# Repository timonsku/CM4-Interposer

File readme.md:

CM4 Interposer
===
Untested design as of 12th September 2021
---

A PCB that helps save the connector cycles on a CM4 by passing through its connection to a second set of Hirose connectors.

Needs:
- 2x DF40C-100DS-0.4V(51)
- 2x DF40C-100DP-0.4V(51)

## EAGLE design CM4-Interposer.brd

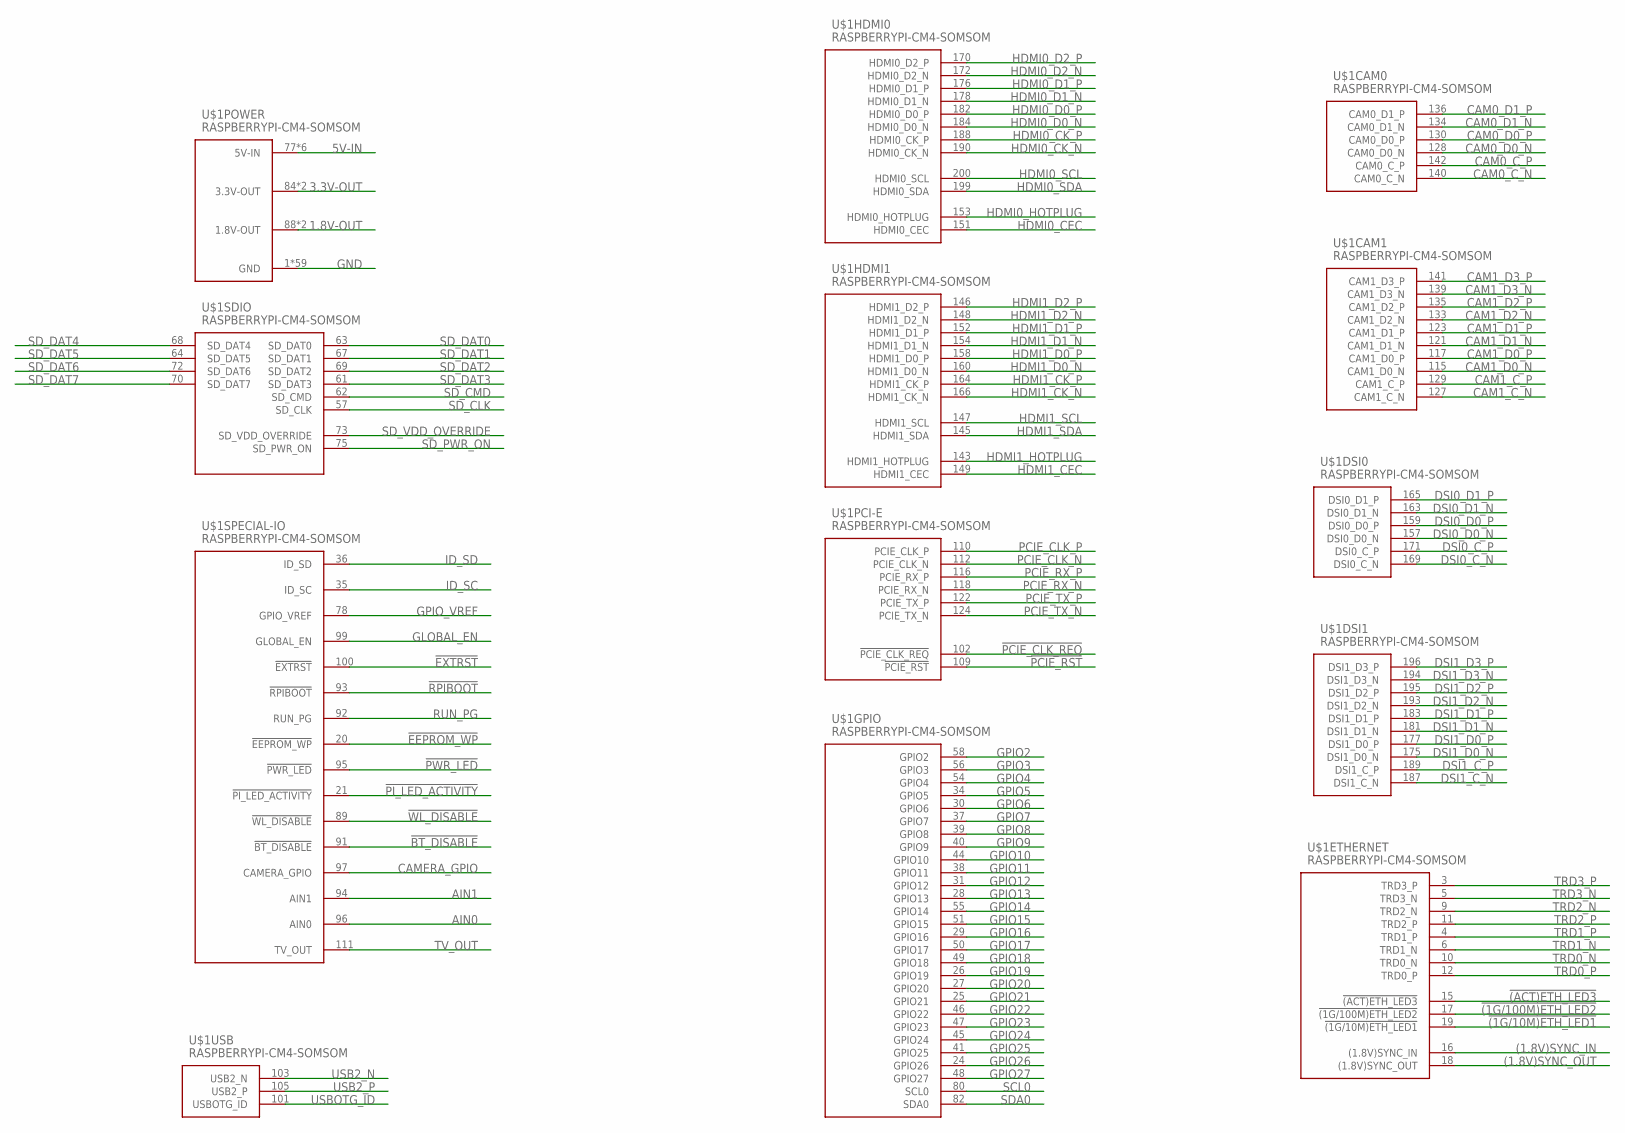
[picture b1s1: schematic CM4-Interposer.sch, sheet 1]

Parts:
U$1: RASPBERRYPI-CM4-SOMSOM; RASPBERRYPI-CM4-PLUG

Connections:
1.8V-OUT: U$1.88 (1.8V-OUT), U$1.90 (1.8V-OUT); also elsewhere on the board
3.3V-OUT: U$1.84 (3.3V-OUT), U$1.86 (3.3V-OUT); also elsewhere on the board
5V-IN: U$1.77 (5V-IN), U$1.79 (5V-IN), U$1.81 (5V-IN), U$1.83 (5V-IN), U$1.85 (5V-IN), U$1.87 (5V-IN); also elsewhere on the board
!(1G/10M)ETH_LED1: U$1.19 (!(1G/10M)ETH_LED1); also elsewhere on the board
!(1G/100M)ETH_LED2: U$1.17 (!(1G/100M)ETH_LED2); also elsewhere on the board
!(ACT)ETH_LED3: U$1.15 (!(ACT)ETH_LED3); also elsewhere on the board
!BT_DISABLE: U$1.91 (!BT_DISABLE); also elsewhere on the board
!EEPROM_WP: U$1.20 (!EEPROM_WP); also elsewhere on the board
!EXTRST: U$1.100 (!EXTRST); also elsewhere on the board
!PCIE_CLK_REQ: U$1.102 (!PCIE_CLK_REQ); also elsewhere on the board
!PCIE_RST: U$1.109 (!PCIE_RST); also elsewhere on the board
!PI_LED_ACTIVITY: U$1.21 (!PI_LED_ACTIVITY); also elsewhere on the board
!PWR_LED: U$1.95 (!PWR_LED); also elsewhere on the board
!RPIBOOT: U$1.93 (!RPIBOOT); also elsewhere on the board
!WL_DISABLE: U$1.89 (!WL_DISABLE); also elsewhere on the board
(1.8V)SYNC_IN: U$1.16 ((1.8V)SYNC_IN); also elsewhere on the board
(1.8V)SYNC_OUT: U$1.18 ((1.8V)SYNC_OUT); also elsewhere on the board
AIN0: U$1.96 (AIN0); also elsewhere on the board
AIN1: U$1.94 (AIN1); also elsewhere on the board
CAM0_C_N: U$1.140 (CAM0_C_N); also elsewhere on the board
CAM0_C_P: U$1.142 (CAM0_C_P); also elsewhere on the board
CAM0_D0_N: U$1.128 (CAM0_D0_N); also elsewhere on the board
CAM0_D0_P: U$1.130 (CAM0_D0_P); also elsewhere on the board
CAM0_D1_N: U$1.134 (CAM0_D1_N); also elsewhere on the board
CAM0_D1_P: U$1.136 (CAM0_D1_P); also elsewhere on the board
CAM1_C_N: U$1.127 (CAM1_C_N); also elsewhere on the board
CAM1_C_P: U$1.129 (CAM1_C_P); also elsewhere on the board
CAM1_D0_N: U$1.115 (CAM1_D0_N); also elsewhere on the board
CAM1_D0_P: U$1.117 (CAM1_D0_P); also elsewhere on the board
CAM1_D1_N: U$1.121 (CAM1_D1_N); also elsewhere on the board
CAM1_D1_P: U$1.123 (CAM1_D1_P); also elsewhere on the board
CAM1_D2_N: U$1.133 (CAM1_D2_N); also elsewhere on the board
CAM1_D2_P: U$1.135 (CAM1_D2_P); also elsewhere on the board
CAM1_D3_N: U$1.139 (CAM1_D3_N); also elsewhere on the board
CAM1_D3_P: U$1.141 (CAM1_D3_P); also elsewhere on the board
CAMERA_GPIO: U$1.97 (CAMERA_GPIO); also elsewhere on the board
DSI0_C_N: U$1.169 (DSI0_C_N); also elsewhere on the board
DSI0_C_P: U$1.171 (DSI0_C_P); also elsewhere on the board
DSI0_D0_N: U$1.157 (DSI0_D0_N); also elsewhere on the board
DSI0_D0_P: U$1.159 (DSI0_D0_P); also elsewhere on the board
DSI0_D1_N: U$1.163 (DSI0_D1_N); also elsewhere on the board
DSI0_D1_P: U$1.165 (DSI0_D1_P); also elsewhere on the board
DSI1_C_N: U$1.187 (DSI1_C_N); also elsewhere on the board
DSI1_C_P: U$1.189 (DSI1_C_P); also elsewhere on the board
DSI1_D0_N: U$1.175 (DSI1_D0_N); also elsewhere on the board
DSI1_D0_P: U$1.177 (DSI1_D0_P); also elsewhere on the board
DSI1_D1_N: U$1.181 (DSI1_D1_N); also elsewhere on the board
DSI1_D1_P: U$1.183 (DSI1_D1_P); also elsewhere on the board
DSI1_D2_N: U$1.193 (DSI1_D2_N); also elsewhere on the board
DSI1_D2_P: U$1.195 (DSI1_D2_P); also elsewhere on the board
DSI1_D3_N: U$1.194 (DSI1_D3_N); also elsewhere on the board
DSI1_D3_P: U$1.196 (DSI1_D3_P); also elsewhere on the board
GLOBAL_EN: U$1.99 (GLOBAL_EN); also elsewhere on the board
GND: U$1.1 (GND), U$1.2 (GND), U$1.7 (GND), U$1.8 (GND), U$1.13 (GND), U$1.14 (GND), U$1.22 (GND), U$1.23 (GND), U$1.32 (GND), U$1.33 (GND), U$1.42 (GND), U$1.43 (GND), U$1.52 (GND), U$1.53 (GND), U$1.59 (GND), U$1.60 (GND), U$1.65 (GND), U$1.66 (GND), U$1.71 (GND), U$1.74 (GND), U$1.98 (GND), U$1.107 (GND), U$1.108 (GND), U$1.113 (GND), U$1.114 (GND), U$1.119 (GND), U$1.120 (GND), U$1.125 (GND), U$1.126 (GND), U$1.131 (GND), U$1.132 (GND), U$1.137 (GND), U$1.138 (GND), U$1.144 (GND), U$1.150 (GND), U$1.155 (GND), U$1.156 (GND), U$1.161 (GND), U$1.162 (GND), U$1.167 (GND), U$1.168 (GND), U$1.173 (GND), U$1.174 (GND), U$1.179 (GND), U$1.180 (GND), U$1.185 (GND), U$1.186 (GND), U$1.191 (GND), U$1.192 (GND), U$1.197 (GND), U$1.198 (GND), U$1.201 (GND), U$1.202 (GND), U$1.203 (GND), U$1.204 (GND), U$1.205 (GND), U$1.206 (GND), U$1.207 (GND), U$1.208 (GND); also elsewhere on the board
GPIO2: U$1.58 (GPIO2); also elsewhere on the board
GPIO3: U$1.56 (GPIO3); also elsewhere on the board
GPIO4: U$1.54 (GPIO4); also elsewhere on the board
GPIO5: U$1.34 (GPIO5); also elsewhere on the board
GPIO6: U$1.30 (GPIO6); also elsewhere on the board
GPIO7: U$1.37 (GPIO7); also elsewhere on the board
GPIO8: U$1.39 (GPIO8); also elsewhere on the board
GPIO9: U$1.40 (GPIO9); also elsewhere on the board
GPIO10: U$1.44 (GPIO10); also elsewhere on the board
GPIO11: U$1.38 (GPIO11); also elsewhere on the board
GPIO12: U$1.31 (GPIO12); also elsewhere on the board
GPIO13: U$1.28 (GPIO13); also elsewhere on the board
GPIO14: U$1.55 (GPIO14); also elsewhere on the board
GPIO15: U$1.51 (GPIO15); also elsewhere on the board
GPIO16: U$1.29 (GPIO16); also elsewhere on the board
GPIO17: U$1.50 (GPIO17); also elsewhere on the board
GPIO18: U$1.49 (GPIO18); also elsewhere on the board
GPIO19: U$1.26 (GPIO19); also elsewhere on the board
GPIO20: U$1.27 (GPIO20); also elsewhere on the board
GPIO21: U$1.25 (GPIO21); also elsewhere on the board
GPIO22: U$1.46 (GPIO22); also elsewhere on the board
GPIO23: U$1.47 (GPIO23); also elsewhere on the board
GPIO24: U$1.45 (GPIO24); also elsewhere on the board
GPIO25: U$1.41 (GPIO25); also elsewhere on the board
GPIO26: U$1.24 (GPIO26); also elsewhere on the board
GPIO27: U$1.48 (GPIO27); also elsewhere on the board
GPIO_VREF: U$1.78 (GPIO_VREF); also elsewhere on the board
HDMI0_CEC: U$1.151 (HDMI0_CEC); also elsewhere on the board
HDMI0_CK_N: U$1.190 (HDMI0_CK_N); also elsewhere on the board
HDMI0_CK_P: U$1.188 (HDMI0_CK_P); also elsewhere on the board
HDMI0_D0_N: U$1.184 (HDMI0_D0_N); also elsewhere on the board
HDMI0_D0_P: U$1.182 (HDMI0_D0_P); also elsewhere on the board
HDMI0_D1_N: U$1.178 (HDMI0_D1_N); also elsewhere on the board
HDMI0_D1_P: U$1.176 (HDMI0_D1_P); also elsewhere on the board
HDMI0_D2_N: U$1.172 (HDMI0_D2_N); also elsewhere on the board
HDMI0_D2_P: U$1.170 (HDMI0_D2_P); also elsewhere on the board
HDMI0_HOTPLUG: U$1.153 (HDMI0_HOTPLUG); also elsewhere on the board
HDMI0_SCL: U$1.200 (HDMI0_SCL); also elsewhere on the board
HDMI0_SDA: U$1.199 (HDMI0_SDA); also elsewhere on the board
HDMI1_CEC: U$1.149 (HDMI1_CEC); also elsewhere on the board
HDMI1_CK_N: U$1.166 (HDMI1_CK_N); also elsewhere on the board
HDMI1_CK_P: U$1.164 (HDMI1_CK_P); also elsewhere on the board
HDMI1_D0_N: U$1.160 (HDMI1_D0_N); also elsewhere on the board
HDMI1_D0_P: U$1.158 (HDMI1_D0_P); also elsewhere on the board
HDMI1_D1_N: U$1.154 (HDMI1_D1_N); also elsewhere on the board
HDMI1_D1_P: U$1.152 (HDMI1_D1_P); also elsewhere on the board
HDMI1_D2_N: U$1.148 (HDMI1_D2_N); also elsewhere on the board
HDMI1_D2_P: U$1.146 (HDMI1_D2_P); also elsewhere on the board
HDMI1_HOTPLUG: U$1.143 (HDMI1_HOTPLUG); also elsewhere on the board
HDMI1_SCL: U$1.147 (HDMI1_SCL); also elsewhere on the board
HDMI1_SDA: U$1.145 (HDMI1_SDA); also elsewhere on the board
ID_SC: U$1.35 (ID_SC); also elsewhere on the board
ID_SD: U$1.36 (ID_SD); also elsewhere on the board
PCIE_CLK_N: U$1.112 (PCIE_CLK_N); also elsewhere on the board
PCIE_CLK_P: U$1.110 (PCIE_CLK_P); also elsewhere on the board
PCIE_RX_N: U$1.118 (PCIE_RX_N); also elsewhere on the board
PCIE_RX_P: U$1.116 (PCIE_RX_P); also elsewhere on the board
PCIE_TX_N: U$1.124 (PCIE_TX_N); also elsewhere on the board
PCIE_TX_P: U$1.122 (PCIE_TX_P); also elsewhere on the board
RUN_PG: U$1.92 (RUN_PG); also elsewhere on the board
SCL0: U$1.80 (SCL0); also elsewhere on the board
SDA0: U$1.82 (SDA0); also elsewhere on the board
SD_CLK: U$1.57 (SD_CLK); also elsewhere on the board
SD_CMD: U$1.62 (SD_CMD); also elsewhere on the board
SD_DAT0: U$1.63 (SD_DAT0); also elsewhere on the board
SD_DAT1: U$1.67 (SD_DAT1); also elsewhere on the board
SD_DAT2: U$1.69 (SD_DAT2); also elsewhere on the board
SD_DAT3: U$1.61 (SD_DAT3); also elsewhere on the board
SD_DAT4: U$1.68 (SD_DAT4); also elsewhere on the board
SD_DAT5: U$1.64 (SD_DAT5); also elsewhere on the board
SD_DAT6: U$1.72 (SD_DAT6); also elsewhere on the board
SD_DAT7: U$1.70 (SD_DAT7); also elsewhere on the board
SD_PWR_ON: U$1.75 (SD_PWR_ON); also elsewhere on the board
SD_VDD_OVERRIDE: U$1.73 (SD_VDD_OVERRIDE); also elsewhere on the board
TRD0_N: U$1.10 (TRD0_N); also elsewhere on the board
TRD0_P: U$1.12 (TRD0_P); also elsewhere on the board
TRD1_N: U$1.6 (TRD1_N); also elsewhere on the board
TRD1_P: U$1.4 (TRD1_P); also elsewhere on the board
TRD2_N: U$1.9 (TRD2_N); also elsewhere on the board
TRD2_P: U$1.11 (TRD2_P); also elsewhere on the board
TRD3_N: U$1.5 (TRD3_N); also elsewhere on the board
TRD3_P: U$1.3 (TRD3_P); also elsewhere on the board
TV_OUT: U$1.111 (TV_OUT); also elsewhere on the board
USB2_N: U$1.103 (USB2_N); also elsewhere on the board
USB2_P: U$1.105 (USB2_P); also elsewhere on the board
USBOTG_ID: U$1.101 (USBOTG_ID); also elsewhere on the board

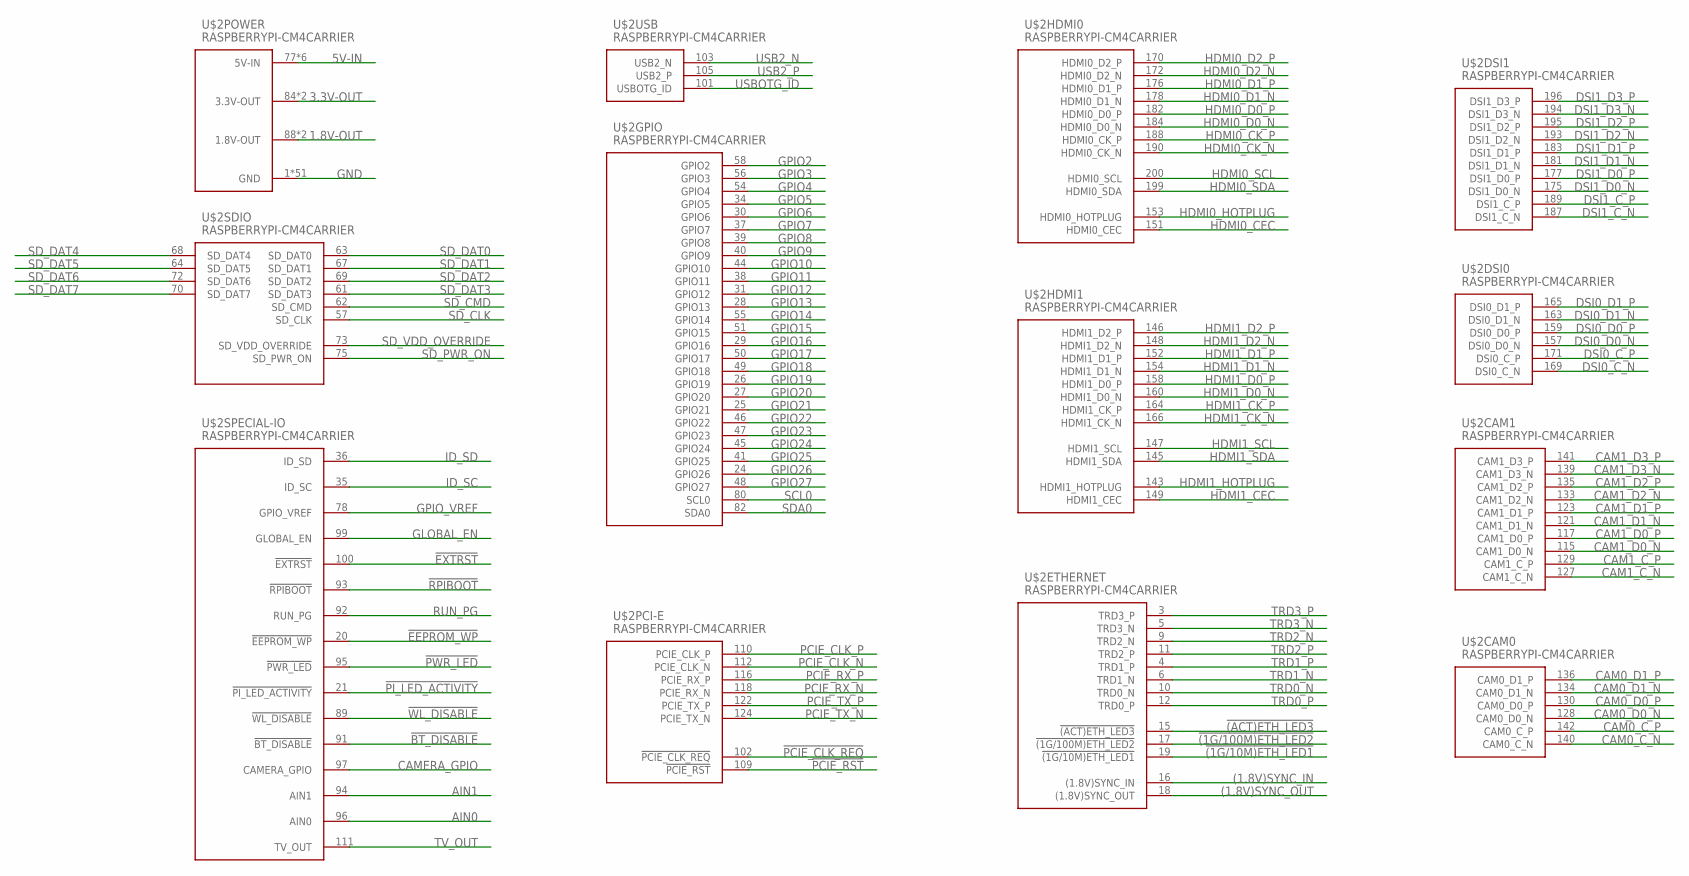
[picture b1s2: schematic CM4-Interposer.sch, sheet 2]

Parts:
U$2: RASPBERRYPI-CM4CARRIER; RASPBERRYPI-CM4

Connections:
1.8V-OUT: U$2.88 (1.8V-OUT), U$2.90 (1.8V-OUT); also elsewhere on the board
3.3V-OUT: U$2.84 (3.3V-OUT), U$2.86 (3.3V-OUT); also elsewhere on the board
5V-IN: U$2.77 (5V-IN), U$2.79 (5V-IN), U$2.81 (5V-IN), U$2.83 (5V-IN), U$2.85 (5V-IN), U$2.87 (5V-IN); also elsewhere on the board
!(1G/10M)ETH_LED1: U$2.19 (!(1G/10M)ETH_LED1); also elsewhere on the board
!(1G/100M)ETH_LED2: U$2.17 (!(1G/100M)ETH_LED2); also elsewhere on the board
!(ACT)ETH_LED3: U$2.15 (!(ACT)ETH_LED3); also elsewhere on the board
!BT_DISABLE: U$2.91 (!BT_DISABLE); also elsewhere on the board
!EEPROM_WP: U$2.20 (!EEPROM_WP); also elsewhere on the board
!EXTRST: U$2.100 (!EXTRST); also elsewhere on the board
!PCIE_CLK_REQ: U$2.102 (!PCIE_CLK_REQ); also elsewhere on the board
!PCIE_RST: U$2.109 (!PCIE_RST); also elsewhere on the board
!PI_LED_ACTIVITY: U$2.21 (!PI_LED_ACTIVITY); also elsewhere on the board
!PWR_LED: U$2.95 (!PWR_LED); also elsewhere on the board
!RPIBOOT: U$2.93 (!RPIBOOT); also elsewhere on the board
!WL_DISABLE: U$2.89 (!WL_DISABLE); also elsewhere on the board
(1.8V)SYNC_IN: U$2.16 ((1.8V)SYNC_IN); also elsewhere on the board
(1.8V)SYNC_OUT: U$2.18 ((1.8V)SYNC_OUT); also elsewhere on the board
AIN0: U$2.96 (AIN0); also elsewhere on the board
AIN1: U$2.94 (AIN1); also elsewhere on the board
CAM0_C_N: U$2.140 (CAM0_C_N); also elsewhere on the board
CAM0_C_P: U$2.142 (CAM0_C_P); also elsewhere on the board
CAM0_D0_N: U$2.128 (CAM0_D0_N); also elsewhere on the board
CAM0_D0_P: U$2.130 (CAM0_D0_P); also elsewhere on the board
CAM0_D1_N: U$2.134 (CAM0_D1_N); also elsewhere on the board
CAM0_D1_P: U$2.136 (CAM0_D1_P); also elsewhere on the board
CAM1_C_N: U$2.127 (CAM1_C_N); also elsewhere on the board
CAM1_C_P: U$2.129 (CAM1_C_P); also elsewhere on the board
CAM1_D0_N: U$2.115 (CAM1_D0_N); also elsewhere on the board
CAM1_D0_P: U$2.117 (CAM1_D0_P); also elsewhere on the board
CAM1_D1_N: U$2.121 (CAM1_D1_N); also elsewhere on the board
CAM1_D1_P: U$2.123 (CAM1_D1_P); also elsewhere on the board
CAM1_D2_N: U$2.133 (CAM1_D2_N); also elsewhere on the board
CAM1_D2_P: U$2.135 (CAM1_D2_P); also elsewhere on the board
CAM1_D3_N: U$2.139 (CAM1_D3_N); also elsewhere on the board
CAM1_D3_P: U$2.141 (CAM1_D3_P); also elsewhere on the board
CAMERA_GPIO: U$2.97 (CAMERA_GPIO); also elsewhere on the board
DSI0_C_N: U$2.169 (DSI0_C_N); also elsewhere on the board
DSI0_C_P: U$2.171 (DSI0_C_P); also elsewhere on the board
DSI0_D0_N: U$2.157 (DSI0_D0_N); also elsewhere on the board
DSI0_D0_P: U$2.159 (DSI0_D0_P); also elsewhere on the board
DSI0_D1_N: U$2.163 (DSI0_D1_N); also elsewhere on the board
DSI0_D1_P: U$2.165 (DSI0_D1_P); also elsewhere on the board
DSI1_C_N: U$2.187 (DSI1_C_N); also elsewhere on the board
DSI1_C_P: U$2.189 (DSI1_C_P); also elsewhere on the board
DSI1_D0_N: U$2.175 (DSI1_D0_N); also elsewhere on the board
DSI1_D0_P: U$2.177 (DSI1_D0_P); also elsewhere on the board
DSI1_D1_N: U$2.181 (DSI1_D1_N); also elsewhere on the board
DSI1_D1_P: U$2.183 (DSI1_D1_P); also elsewhere on the board
DSI1_D2_N: U$2.193 (DSI1_D2_N); also elsewhere on the board
DSI1_D2_P: U$2.195 (DSI1_D2_P); also elsewhere on the board
DSI1_D3_N: U$2.194 (DSI1_D3_N); also elsewhere on the board
DSI1_D3_P: U$2.196 (DSI1_D3_P); also elsewhere on the board
GLOBAL_EN: U$2.99 (GLOBAL_EN); also elsewhere on the board
GND: U$2.1 (GND), U$2.2 (GND), U$2.7 (GND), U$2.8 (GND), U$2.13 (GND), U$2.14 (GND), U$2.22 (GND), U$2.23 (GND), U$2.32 (GND), U$2.33 (GND), U$2.42 (GND), U$2.43 (GND), U$2.52 (GND), U$2.53 (GND), U$2.59 (GND), U$2.60 (GND), U$2.65 (GND), U$2.66 (GND), U$2.71 (GND), U$2.74 (GND), U$2.98 (GND), U$2.107 (GND), U$2.108 (GND), U$2.113 (GND), U$2.114 (GND), U$2.119 (GND), U$2.120 (GND), U$2.125 (GND), U$2.126 (GND), U$2.131 (GND), U$2.132 (GND), U$2.137 (GND), U$2.138 (GND), U$2.144 (GND), U$2.150 (GND), U$2.155 (GND), U$2.156 (GND), U$2.161 (GND), U$2.162 (GND), U$2.167 (GND), U$2.168 (GND), U$2.173 (GND), U$2.174 (GND), U$2.179 (GND), U$2.180 (GND), U$2.185 (GND), U$2.186 (GND), U$2.191 (GND), U$2.192 (GND), U$2.197 (GND), U$2.198 (GND); also elsewhere on the board
GPIO2: U$2.58 (GPIO2); also elsewhere on the board
GPIO3: U$2.56 (GPIO3); also elsewhere on the board
GPIO4: U$2.54 (GPIO4); also elsewhere on the board
GPIO5: U$2.34 (GPIO5); also elsewhere on the board
GPIO6: U$2.30 (GPIO6); also elsewhere on the board
GPIO7: U$2.37 (GPIO7); also elsewhere on the board
GPIO8: U$2.39 (GPIO8); also elsewhere on the board
GPIO9: U$2.40 (GPIO9); also elsewhere on the board
GPIO10: U$2.44 (GPIO10); also elsewhere on the board
GPIO11: U$2.38 (GPIO11); also elsewhere on the board
GPIO12: U$2.31 (GPIO12); also elsewhere on the board
GPIO13: U$2.28 (GPIO13); also elsewhere on the board
GPIO14: U$2.55 (GPIO14); also elsewhere on the board
GPIO15: U$2.51 (GPIO15); also elsewhere on the board
GPIO16: U$2.29 (GPIO16); also elsewhere on the board
GPIO17: U$2.50 (GPIO17); also elsewhere on the board
GPIO18: U$2.49 (GPIO18); also elsewhere on the board
GPIO19: U$2.26 (GPIO19); also elsewhere on the board
GPIO20: U$2.27 (GPIO20); also elsewhere on the board
GPIO21: U$2.25 (GPIO21); also elsewhere on the board
GPIO22: U$2.46 (GPIO22); also elsewhere on the board
GPIO23: U$2.47 (GPIO23); also elsewhere on the board
GPIO24: U$2.45 (GPIO24); also elsewhere on the board
GPIO25: U$2.41 (GPIO25); also elsewhere on the board
GPIO26: U$2.24 (GPIO26); also elsewhere on the board
GPIO27: U$2.48 (GPIO27); also elsewhere on the board
GPIO_VREF: U$2.78 (GPIO_VREF); also elsewhere on the board
HDMI0_CEC: U$2.151 (HDMI0_CEC); also elsewhere on the board
HDMI0_CK_N: U$2.190 (HDMI0_CK_N); also elsewhere on the board
HDMI0_CK_P: U$2.188 (HDMI0_CK_P); also elsewhere on the board
HDMI0_D0_N: U$2.184 (HDMI0_D0_N); also elsewhere on the board
HDMI0_D0_P: U$2.182 (HDMI0_D0_P); also elsewhere on the board
HDMI0_D1_N: U$2.178 (HDMI0_D1_N); also elsewhere on the board
HDMI0_D1_P: U$2.176 (HDMI0_D1_P); also elsewhere on the board
HDMI0_D2_N: U$2.172 (HDMI0_D2_N); also elsewhere on the board
HDMI0_D2_P: U$2.170 (HDMI0_D2_P); also elsewhere on the board
HDMI0_HOTPLUG: U$2.153 (HDMI0_HOTPLUG); also elsewhere on the board
HDMI0_SCL: U$2.200 (HDMI0_SCL); also elsewhere on the board
HDMI0_SDA: U$2.199 (HDMI0_SDA); also elsewhere on the board
HDMI1_CEC: U$2.149 (HDMI1_CEC); also elsewhere on the board
HDMI1_CK_N: U$2.166 (HDMI1_CK_N); also elsewhere on the board
HDMI1_CK_P: U$2.164 (HDMI1_CK_P); also elsewhere on the board
HDMI1_D0_N: U$2.160 (HDMI1_D0_N); also elsewhere on the board
HDMI1_D0_P: U$2.158 (HDMI1_D0_P); also elsewhere on the board
HDMI1_D1_N: U$2.154 (HDMI1_D1_N); also elsewhere on the board
HDMI1_D1_P: U$2.152 (HDMI1_D1_P); also elsewhere on the board
HDMI1_D2_N: U$2.148 (HDMI1_D2_N); also elsewhere on the board
HDMI1_D2_P: U$2.146 (HDMI1_D2_P); also elsewhere on the board
HDMI1_HOTPLUG: U$2.143 (HDMI1_HOTPLUG); also elsewhere on the board
HDMI1_SCL: U$2.147 (HDMI1_SCL); also elsewhere on the board
HDMI1_SDA: U$2.145 (HDMI1_SDA); also elsewhere on the board
ID_SC: U$2.35 (ID_SC); also elsewhere on the board
ID_SD: U$2.36 (ID_SD); also elsewhere on the board
PCIE_CLK_N: U$2.112 (PCIE_CLK_N); also elsewhere on the board
PCIE_CLK_P: U$2.110 (PCIE_CLK_P); also elsewhere on the board
PCIE_RX_N: U$2.118 (PCIE_RX_N); also elsewhere on the board
PCIE_RX_P: U$2.116 (PCIE_RX_P); also elsewhere on the board
PCIE_TX_N: U$2.124 (PCIE_TX_N); also elsewhere on the board
PCIE_TX_P: U$2.122 (PCIE_TX_P); also elsewhere on the board
RUN_PG: U$2.92 (RUN_PG); also elsewhere on the board
SCL0: U$2.80 (SCL0); also elsewhere on the board
SDA0: U$2.82 (SDA0); also elsewhere on the board
SD_CLK: U$2.57 (SD_CLK); also elsewhere on the board
SD_CMD: U$2.62 (SD_CMD); also elsewhere on the board
SD_DAT0: U$2.63 (SD_DAT0); also elsewhere on the board
SD_DAT1: U$2.67 (SD_DAT1); also elsewhere on the board
SD_DAT2: U$2.69 (SD_DAT2); also elsewhere on the board
SD_DAT3: U$2.61 (SD_DAT3); also elsewhere on the board
SD_DAT4: U$2.68 (SD_DAT4); also elsewhere on the board
SD_DAT5: U$2.64 (SD_DAT5); also elsewhere on the board
SD_DAT6: U$2.72 (SD_DAT6); also elsewhere on the board
SD_DAT7: U$2.70 (SD_DAT7); also elsewhere on the board
SD_PWR_ON: U$2.75 (SD_PWR_ON); also elsewhere on the board
SD_VDD_OVERRIDE: U$2.73 (SD_VDD_OVERRIDE); also elsewhere on the board
TRD0_N: U$2.10 (TRD0_N); also elsewhere on the board
TRD0_P: U$2.12 (TRD0_P); also elsewhere on the board
TRD1_N: U$2.6 (TRD1_N); also elsewhere on the board
TRD1_P: U$2.4 (TRD1_P); also elsewhere on the board
TRD2_N: U$2.9 (TRD2_N); also elsewhere on the board
TRD2_P: U$2.11 (TRD2_P); also elsewhere on the board
TRD3_N: U$2.5 (TRD3_N); also elsewhere on the board
TRD3_P: U$2.3 (TRD3_P); also elsewhere on the board
TV_OUT: U$2.111 (TV_OUT); also elsewhere on the board
USB2_N: U$2.103 (USB2_N); also elsewhere on the board
USB2_P: U$2.105 (USB2_P); also elsewhere on the board
USBOTG_ID: U$2.101 (USBOTG_ID); also elsewhere on the board

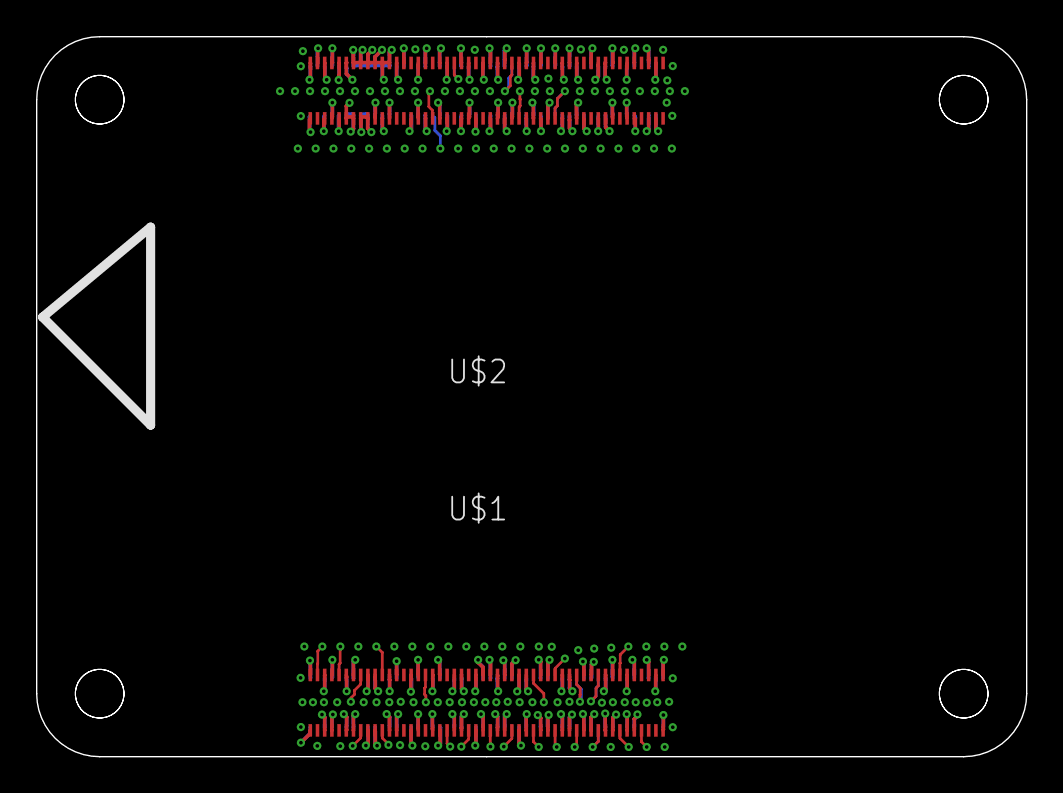
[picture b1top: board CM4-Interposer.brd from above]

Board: 4 copper layers, 55.0 x 40.0 mm, 3 parts (1 on the bottom side), 140 nets.

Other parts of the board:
U$3: DIODES-DELIGHT-LOGO-15X15-BTM

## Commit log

2021-09-11 add readme
2021-09-11 misc

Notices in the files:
parts and their libraries:
Custom-Parts: License: CC-BY-SA
